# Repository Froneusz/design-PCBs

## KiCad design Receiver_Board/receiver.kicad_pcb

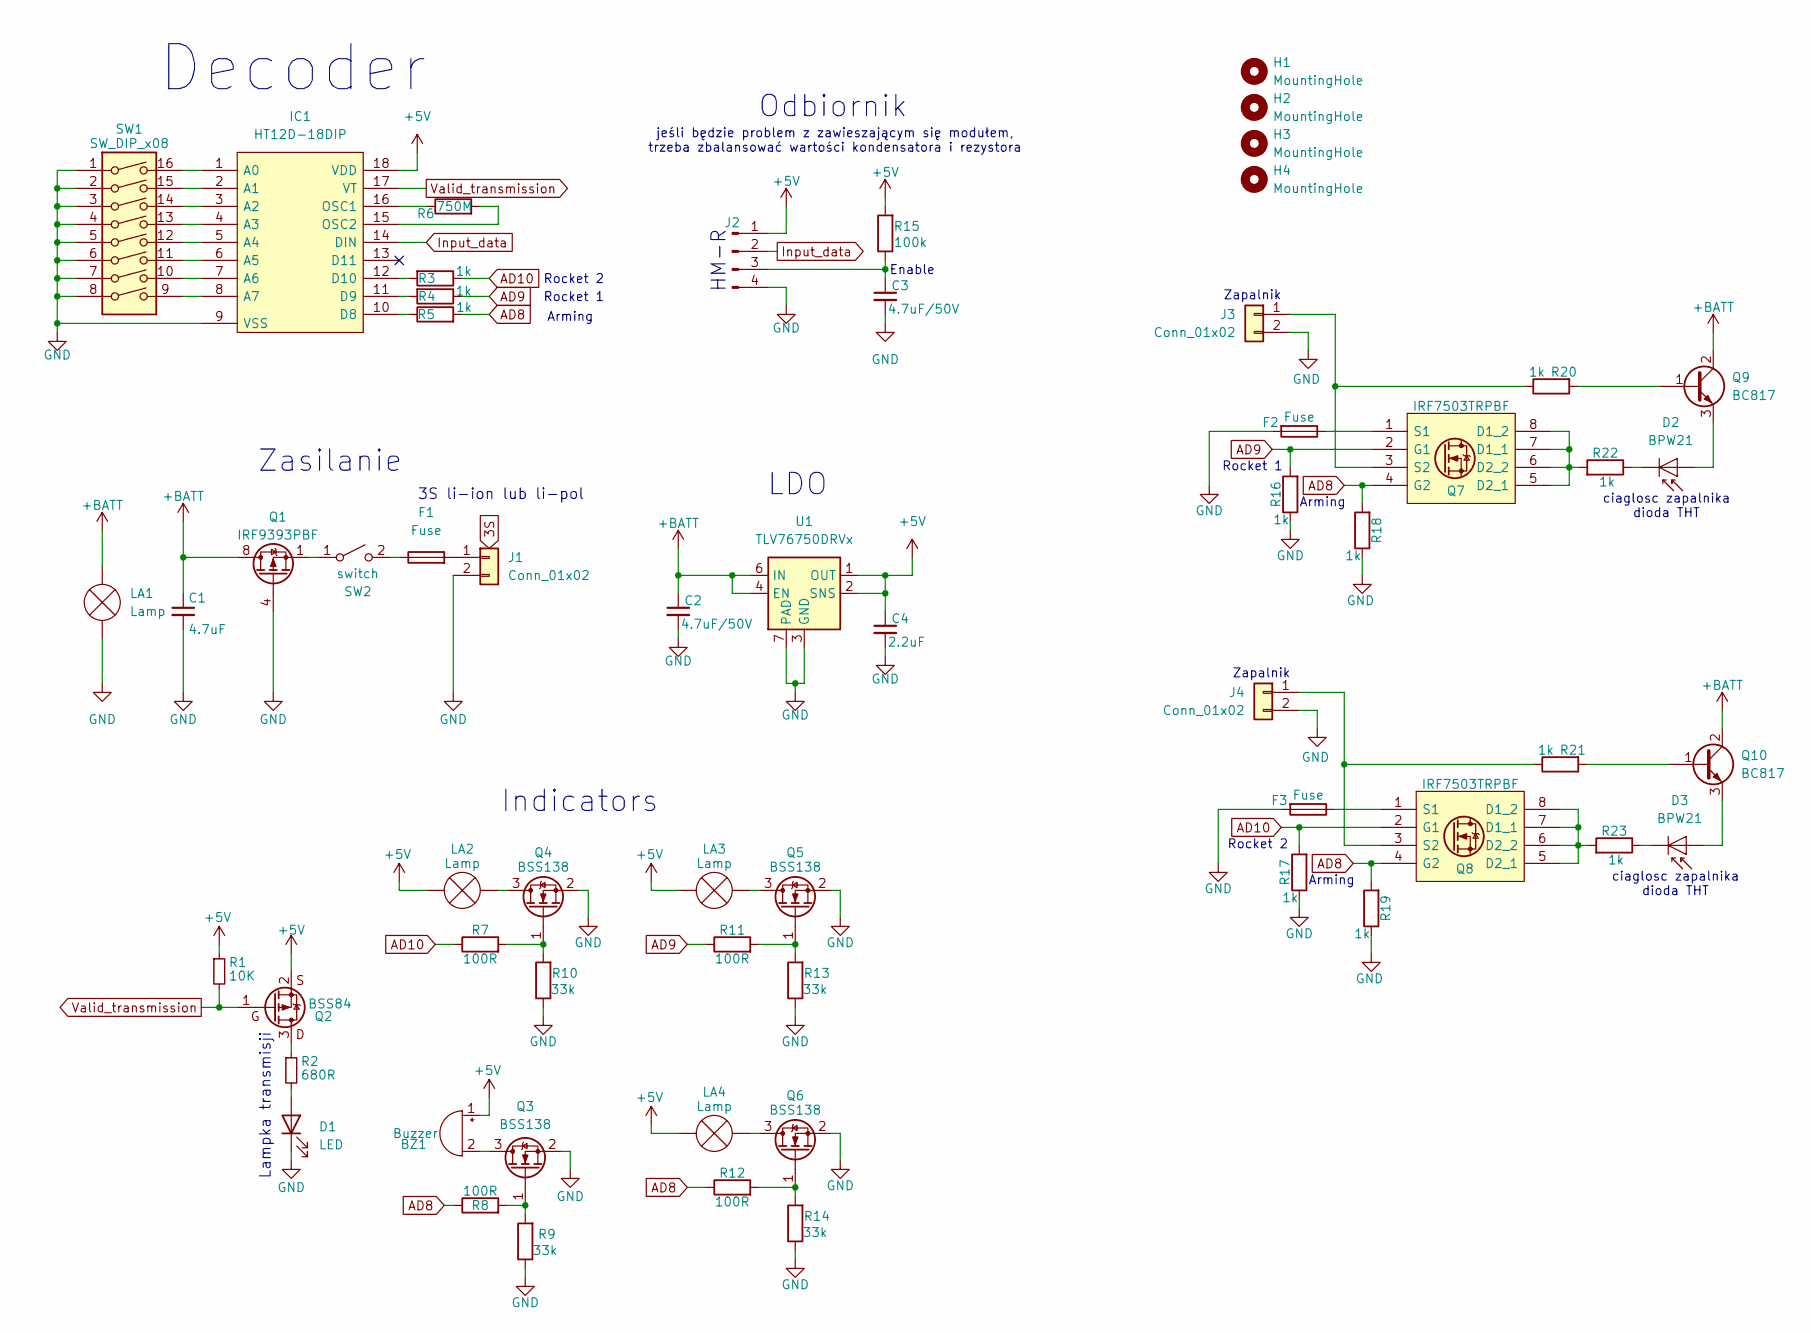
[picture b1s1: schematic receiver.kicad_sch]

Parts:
BZ1: Buzzer; PinHeader_1x02_P2.54mm_Vertical_led_relayboard_lpbox
C1: 4.7uF; C_0805_2012Metric_Pad1.18x1.45mm_HandSolder
C2, C3: 4.7uF/50V; C_0805_2012Metric_Pad1.18x1.45mm_HandSolder
C4: 2.2uF; C_0805_2012Metric_Pad1.18x1.45mm_HandSolder
D1: LED; LED_0603_1608Metric_Pad1.05x0.95mm_HandSolder
D2, D3: BPW21; PinHeader_1x02_P2.54mm_Vertical_led_relayboard_lpbox
F1, F2, F3: Fuse; Fuse_0805_2012Metric_Pad1.15x1.40mm_HandSolder
H1, H2, H3, H4: MountingHole; MountingHole_3.2mm_M3
IC1: HT12D-18DIP; DIP18 HT12; Manufacturer_Part_Number HT12D-18DIP
J1: Conn_01x02; XY2500R-DS(5.08)-02P
J2: Conn_01x04_Pin; PinHeader_1x04_P2.54mm_Vertical
J3, J4: Conn_01x02; PhoenixContact_MCV_1,5_2-G-3.5_1x02_P3.50mm_Vertical
LA1, LA2, LA3, LA4: Lamp; PinHeader_1x02_P2.54mm_Vertical_led_relayboard_lpbox
Q1: IRF9393PBF; SOIC-8_3.9x4.9mm_P1.27mm
Q2: BSS84; SOT-23
Q3, Q4, Q5, Q6: BSS138; SOT-23
Q7, Q8: IRF7503TRPBF; SOP65P490X110-8N; Mouser Part Number 942-IRF7503TRPBF
Q9, Q10: BC817; SOT-23_Handsoldering
R1: 10K; R_0603_1608Metric_Pad0.98x0.95mm_HandSolder
R2: 680R; R_0603_1608Metric_Pad0.98x0.95mm_HandSolder
R3, R4, R5, R16, R17, R18, R19, R20, R21, R22, R23: 1k; R_0603_1608Metric_Pad0.98x0.95mm_HandSolder
R6: 750M; R_0603_1608Metric_Pad0.98x0.95mm_HandSolder
R7, R8, R11, R12: 100R; R_0603_1608Metric_Pad0.98x0.95mm_HandSolder
R9, R10, R13, R14: 33k; R_0603_1608Metric_Pad0.98x0.95mm_HandSolder
R15: 100k; R_0603_1608Metric_Pad0.98x0.95mm_HandSolder
SW1: SW_DIP_x08; 2198MSTR
SW2: switch; PinHeader_1x02_P2.54mm_Vertical_led_relayboard_lpbox
U1: TLV76750DRVx; WSON-6-1EP_2x2mm_P0.65mm_EP1x1.6mm_ThermalVias

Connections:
+5V: BZ1.1 (+), C4.1, IC1.18 (VDD), J2.1, LA2.2 (+), LA3.2 (+), LA4.2 (+), Q2.2 (S), R1.1, R15.2, U1.1 (OUT), U1.2 (SNS)
+BATT: C1.1, C2.1, LA1.2 (+), Q1.5 (D), Q1.6 (D), Q1.7 (D), Q1.8 (D), Q9.2 (C), Q10.2 (C), U1.4 (EN), U1.6 (IN)
AD8: Q7.4 (G2), Q8.4 (G2), R5.2, R8.1, R12.1, R18.2, R19.2
AD9: Q7.2 (G1), R4.1, R11.1, R16.2
AD10: Q8.2 (G1), R3.1, R7.1, R17.2
GND: C1.2, C2.2, C3.2, C4.2, D1.1 (K), F2.2, F3.2, IC1.9 (VSS), J1.2, J2.4, J3.2, J4.2, LA1.1 (-), Q1.4 (G), Q3.2 (S), Q4.2 (S), Q5.2 (S), Q6.2 (S), R9.1, R10.1, R13.1, R14.1, R16.1, R17.1, R18.1, R19.1, SW1.1, SW1.2, SW1.3, SW1.4, SW1.5, SW1.6, SW1.7, SW1.8, U1.3 (GND), U1.5 (GND), U1.7 (PAD)
Input_data: IC1.14 (DIN), J2.2
unnamed: BZ1.2 (-), Q3.3 (D)
unnamed: D1.2 (A), R2.2
unnamed: D2.1 (A), Q9.3 (E)
unnamed: D2.2 (K), R22.1
unnamed: D3.1 (A), Q10.3 (E)
unnamed: D3.2 (K), R23.1
unnamed: IC1.1 (A0), SW1.16
unnamed: IC1.2 (A1), SW1.15
unnamed: IC1.3 (A2), SW1.14
unnamed: IC1.4 (A3), SW1.13
unnamed: IC1.5 (A4), SW1.12
unnamed: IC1.6 (A5), SW1.11
unnamed: IC1.7 (A6), SW1.10
unnamed: IC1.8 (A7), SW1.9
unnamed: IC1.10 (D8), R5.1
unnamed: IC1.11 (D9), R4.2
unnamed: IC1.12 (D10), R3.2
unnamed: IC1.16 (OSC1), R6.1
unnamed: IC1.15 (OSC2), R6.2
unnamed: F1.2, J1.1
unnamed: C3.1, J2.3, R15.1
unnamed: J3.1, Q7.3 (S2), R20.1
unnamed: J4.1, Q8.3 (S2), R21.1
unnamed: LA2.1 (-), Q4.3 (D)
unnamed: LA3.1 (-), Q5.3 (D)
unnamed: LA4.1 (-), Q6.3 (D)
unnamed: Q2.3 (D), R2.1
unnamed: Q3.1 (G), R8.2, R9.2
unnamed: Q4.1 (G), R7.2, R10.2
unnamed: Q5.1 (G), R11.2, R13.2
unnamed: Q6.1 (G), R12.2, R14.2
unnamed: Q7.5 (D2_1), Q7.6 (D2_2), Q7.7 (D1_1), Q7.8 (D1_2), R22.2
unnamed: F2.1, Q7.1 (S1)
unnamed: Q8.5 (D2_1), Q8.6 (D2_2), Q8.7 (D1_1), Q8.8 (D1_2), R23.2
unnamed: F3.1, Q8.1 (S1)
unnamed: Q9.1 (B), R20.2
unnamed: Q10.1 (B), R21.2
unnamed: Q1.1 (S), Q1.2 (S), Q1.3 (S), SW2.1 (A)
unnamed: F1.1, SW2.2 (B)
Valid_transmission: IC1.17 (VT), Q2.1 (G), R1.2

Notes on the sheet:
Rocket 1
LDO
jeśli będzie problem z zawieszającym się modułem, trzeba zbalansować wartości kondensatora i rezystora
Zasilanie
ciaglosc zapalnika dioda THT
Arming
Indicators
Rocket 2
Lampka transmisji
Odbiornik
Enable
HM-R
Zapalnik
Decoder
3S li-ion lub li-pol

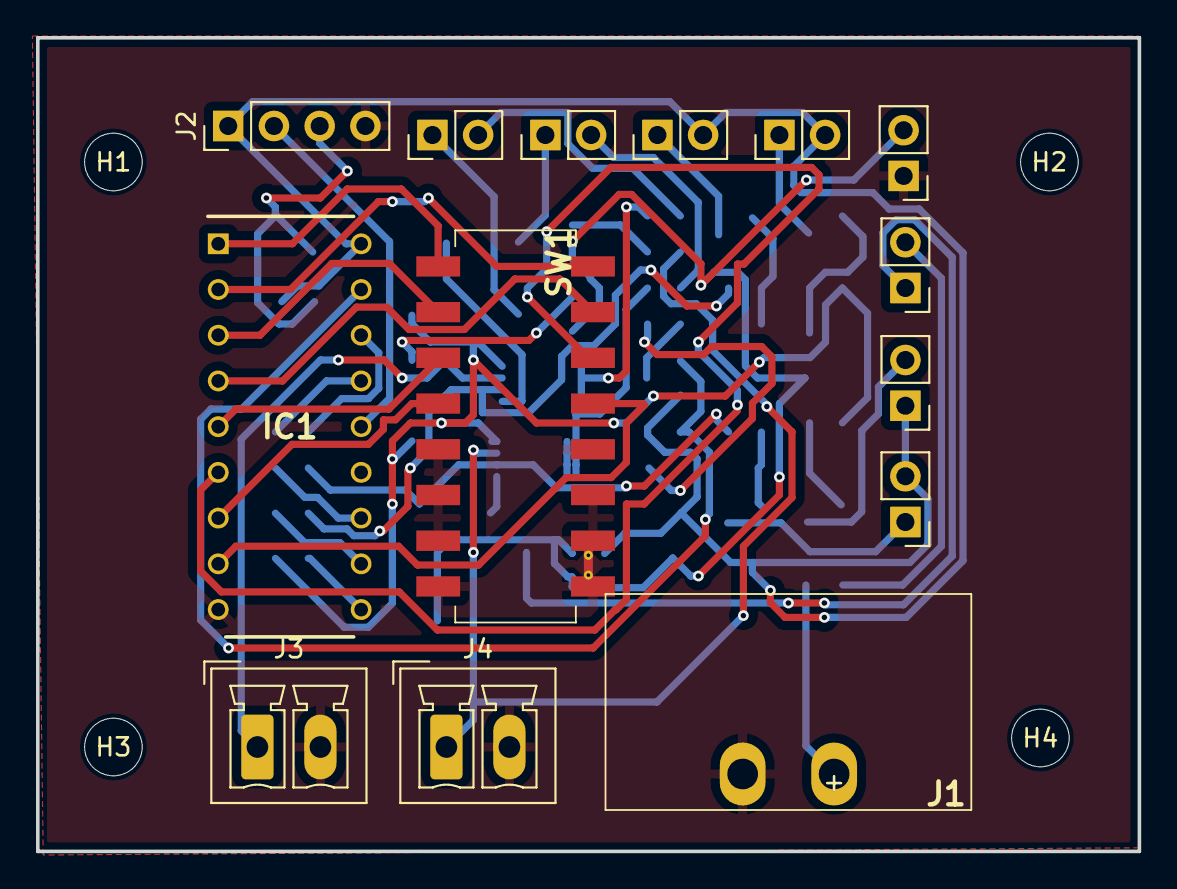
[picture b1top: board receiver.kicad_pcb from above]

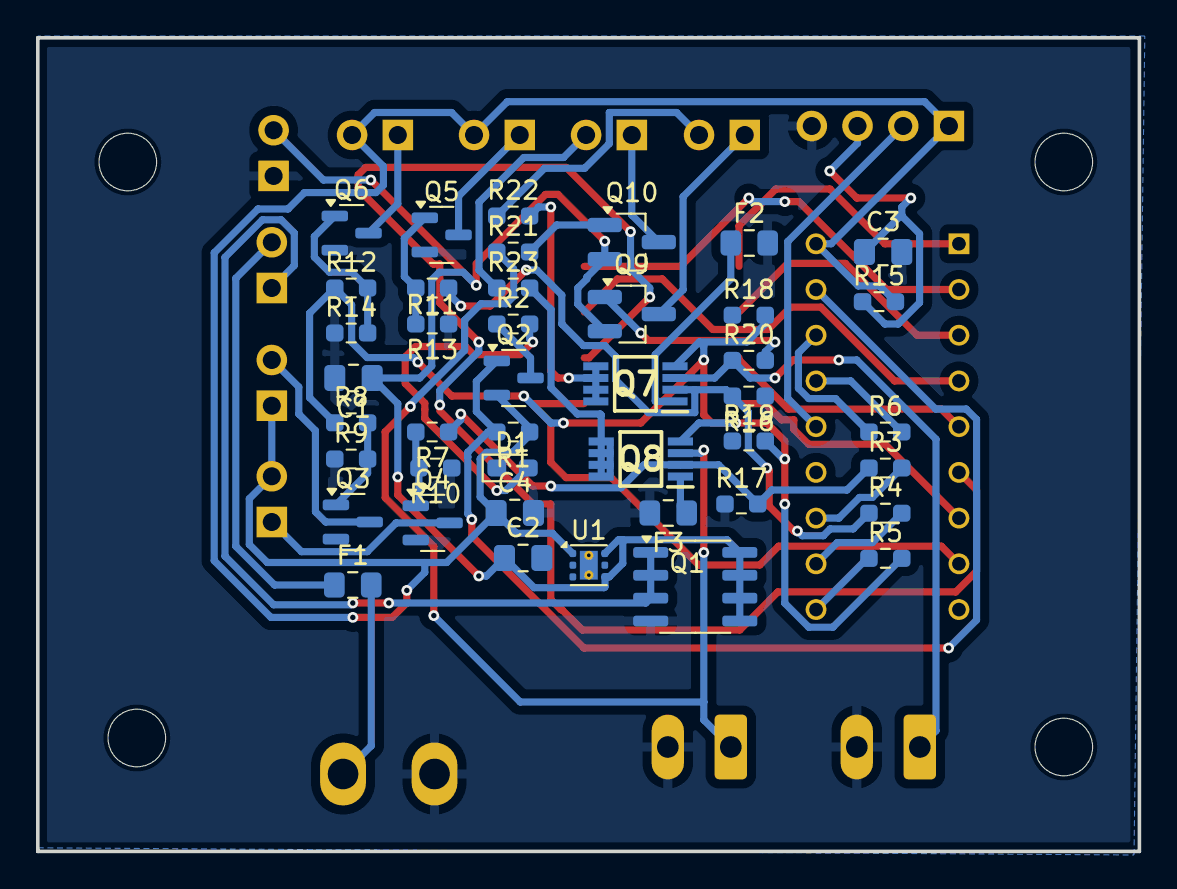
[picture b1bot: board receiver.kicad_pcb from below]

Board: 2 copper layers, 61.2 x 45.2 mm, 60 parts (42 on the bottom side), 47 nets.

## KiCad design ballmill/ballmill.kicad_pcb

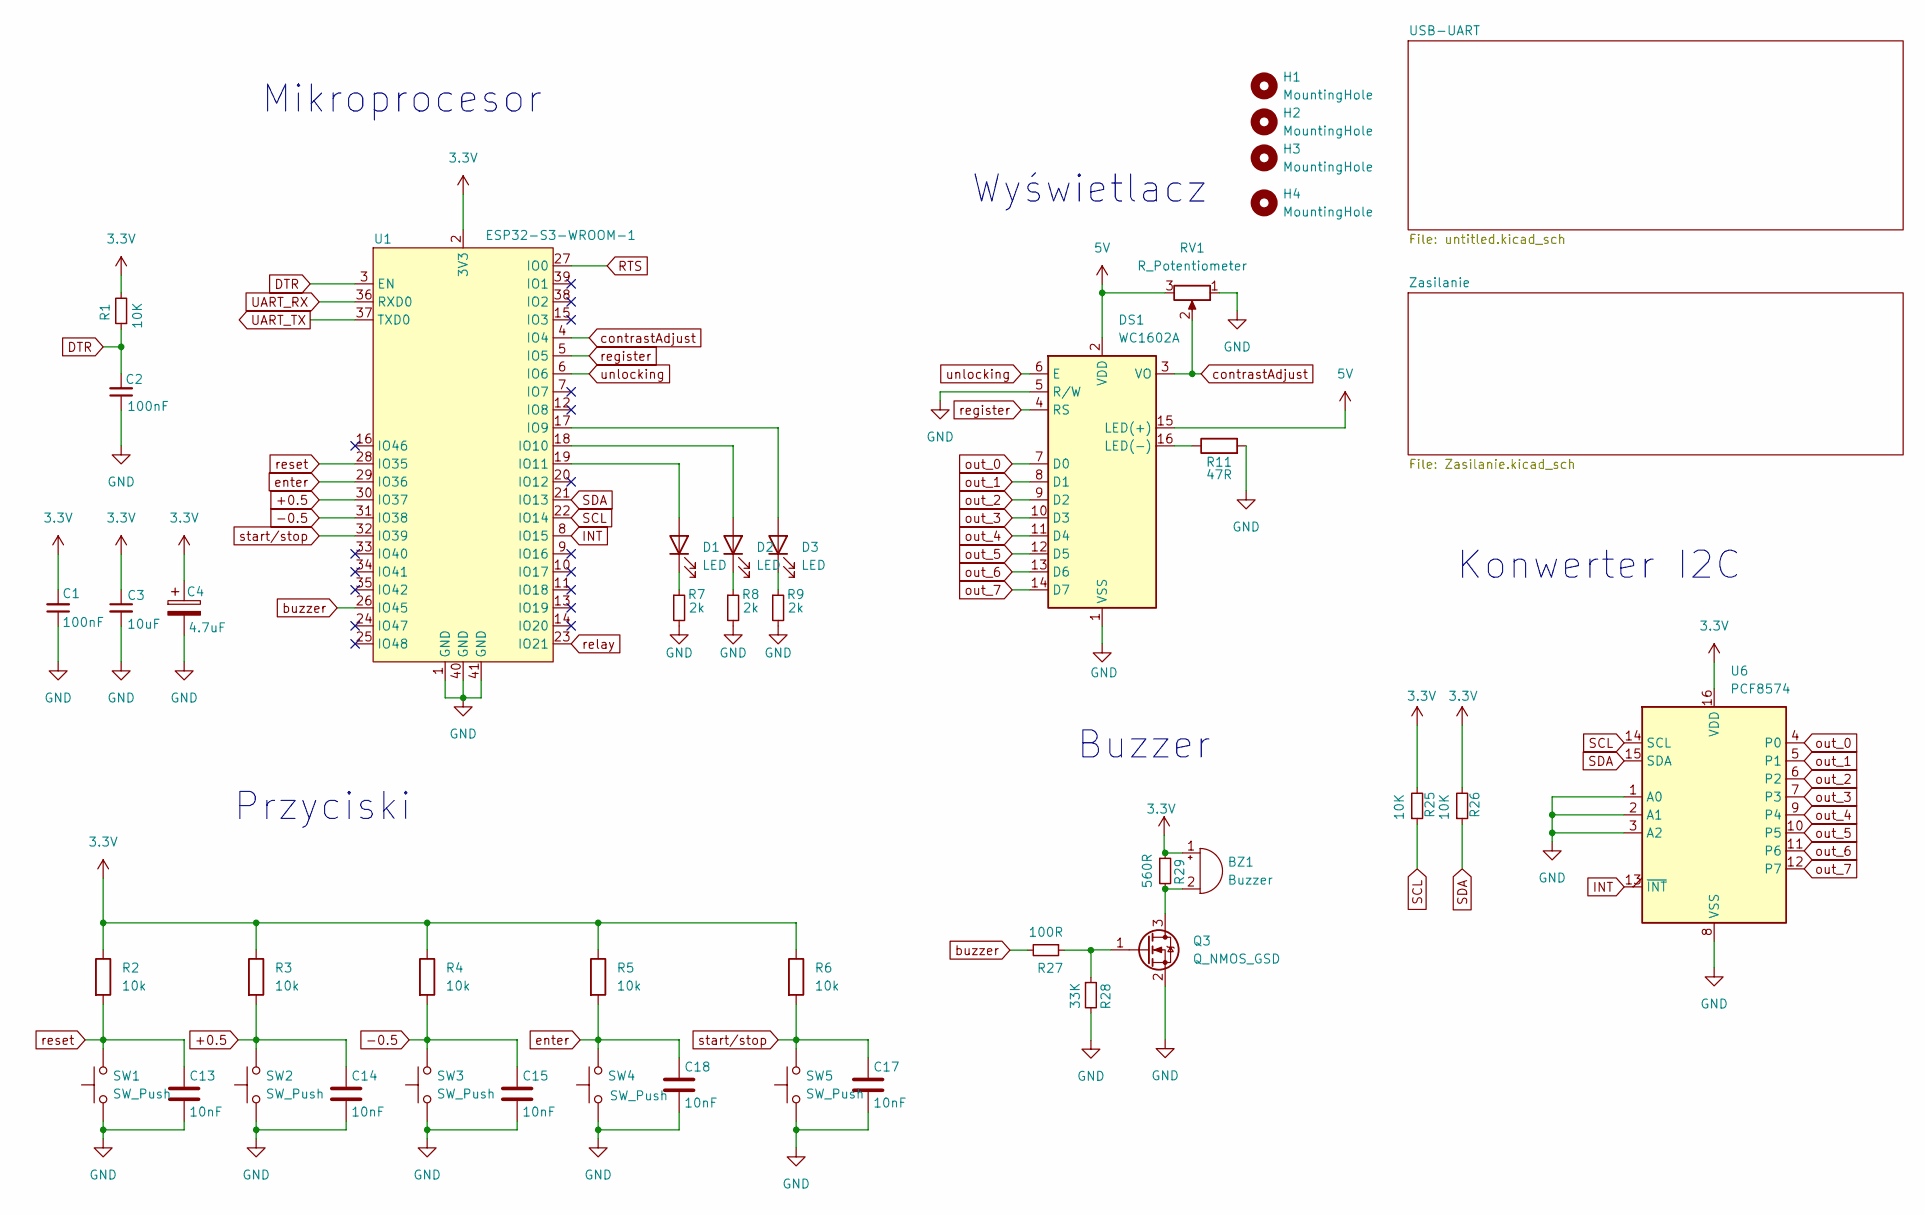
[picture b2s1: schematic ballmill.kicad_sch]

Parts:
BZ1: Buzzer; CMI9605IC0580T
C1, C2: 100nF; C_0603_1608Metric_Pad1.08x0.95mm_HandSolder
C3: 10uF; C_0603_1608Metric_Pad1.08x0.95mm_HandSolder
C4: 4.7uF; C_0603_1608Metric_Pad1.08x0.95mm_HandSolder
C13, C14, C15, C17, C18: 10nF; C_0603_1608Metric_Pad1.08x0.95mm_HandSolder
D1, D2, D3: LED; LED_0805_2012Metric_Pad1.15x1.40mm_HandSolder
DS1: WC1602A
H1, H2, H3, H4: MountingHole; MountingHole_3.2mm_M3
Q3: Q_NMOS_GSD; SOT-23_Handsoldering
R1, R25, R26: 10K; R_0603_1608Metric_Pad0.98x0.95mm_HandSolder
R2, R3, R4, R5, R6: 10k; R_0603_1608Metric_Pad0.98x0.95mm_HandSolder
R7, R8, R9: 2k; R_0603_1608Metric_Pad0.98x0.95mm_HandSolder
R11: 47R; R_0603_1608Metric_Pad0.98x0.95mm_HandSolder
R27: 100R; R_0603_1608Metric_Pad0.98x0.95mm_HandSolder
R28: 33K; R_0603_1608Metric_Pad0.98x0.95mm_HandSolder
R29: 560R; R_0603_1608Metric_Pad0.98x0.95mm_HandSolder
RV1: R_Potentiometer; Potentiometer_Bourns_3296W_Vertical
SW1, SW2, SW3, SW4, SW5: SW_Push; SW_PUSH_6mm
U1: ESP32-S3-WROOM-1
U6: PCF8574; QFN50P300X300X100-17N-D

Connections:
3.3V: BZ1.1 (-), C1.2, C3.1, C4.1, R1.2, R2.1, R3.1, R4.1, R5.1, R6.1, R25.2, R26.2, R29.1, U1.2 (3V3), U6.16 (VDD); also elsewhere on the board
5V: DS1.2 (VDD), DS1.15 (LED(+)), RV1.3; also elsewhere on the board
+0.5: C14.2, R3.2, SW2.2, U1.30 (IO37)
-0.5: C15.2, R4.2, SW3.2, U1.31 (IO38)
DTR: C2.2, R1.1, U1.3 (EN); also elsewhere on the board
GND: C1.1, C2.1, C3.2, C4.2, C13.1, C14.1, C15.1, C17.1, C18.1, DS1.1 (VSS), DS1.5 (R/W), Q3.2 (S), R7.2, R8.2, R9.2, R11.2, R28.2, RV1.1, SW1.1, SW2.1, SW3.1, SW4.1, SW5.1, U1.1 (GND), U1.40 (GND), U1.41 (GND), U6.1 (A0), U6.2 (A1), U6.3 (A2), U6.8 (VSS); also elsewhere on the board
INT: U1.8 (IO15), U6.13 (~INT)
unnamed: BZ1.2 (+), Q3.3 (D), R29.2
unnamed: D1.2 (A), U1.19 (IO11)
unnamed: D1.1 (K), R7.1
unnamed: D2.2 (A), U1.18 (IO10)
unnamed: D2.1 (K), R8.1
unnamed: D3.2 (A), U1.17 (IO9)
unnamed: D3.1 (K), R9.1
unnamed: DS1.16 (LED(-)), R11.1
unnamed: Q3.1 (G), R27.1, R28.1
RTS: U1.27 (IO0); also elsewhere on the board
SCL: R25.1, U1.22 (IO14), U6.14 (SCL)
SDA: R26.1, U1.21 (IO13), U6.15 (SDA)
UART_RX: U1.36 (RXD0); also elsewhere on the board
UART_TX: U1.37 (TXD0); also elsewhere on the board
buzzer: R27.2, U1.26 (IO45)
contrastAdjust: DS1.3 (VO), RV1.2, U1.4 (IO4)
enter: C18.2, R5.2, SW4.2, U1.29 (IO36)
out_0: DS1.7 (D0), U6.4 (P0)
out_1: DS1.8 (D1), U6.5 (P1)
out_2: DS1.9 (D2), U6.6 (P2)
out_3: DS1.10 (D3), U6.7 (P3)
out_4: DS1.11 (D4), U6.9 (P4)
out_5: DS1.12 (D5), U6.10 (P5)
out_6: DS1.13 (D6), U6.11 (P6)
out_7: DS1.14 (D7), U6.12 (P7)
register: DS1.4 (RS), U1.5 (IO5)
relay: U1.23 (IO21); also elsewhere on the board
reset: C13.2, R2.2, SW1.2, U1.28 (IO35)
start/stop: C17.2, R6.2, SW5.2, U1.32 (IO39)
unlocking: DS1.6 (E), U1.6 (IO6)

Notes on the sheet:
Mikroprocesor
Konwerter I2C
Buzzer
Wyświetlacz
Przyciski

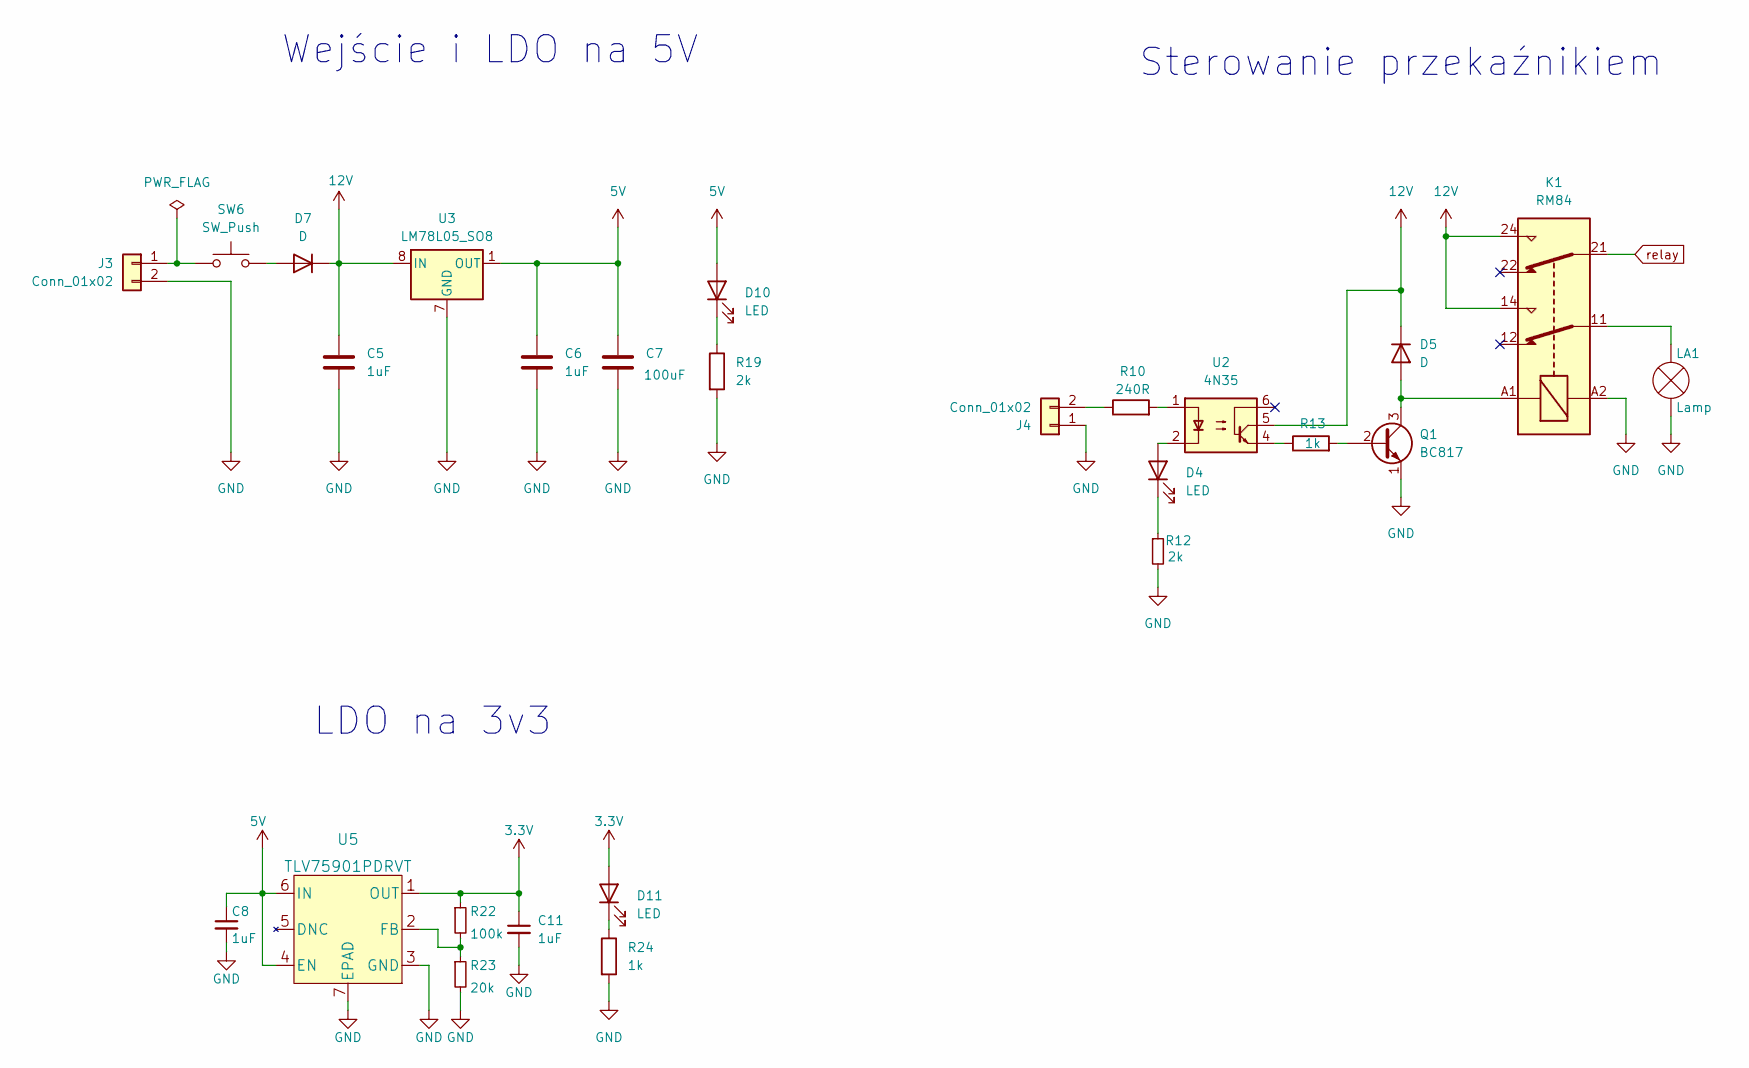
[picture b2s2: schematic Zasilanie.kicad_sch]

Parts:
C5, C6, C8, C11: 1uF; C_0805_2012Metric_Pad1.18x1.45mm_HandSolder
C7: 100uF; C_0805_2012Metric_Pad1.18x1.45mm_HandSolder
D4, D10, D11: LED; LED_0805_2012Metric_Pad1.15x1.40mm_HandSolder
D5: D; PinHeader_1x02_P2.54mm_Vertical_led_relayboard_lpbox
D7: D; D_0805_2012Metric_Pad1.15x1.40mm_HandSolder
J3, J4: Conn_01x02; XY2500R-DS(5.08)-02P
K1: RM84; Relay_DPDT_Finder_40.52
LA1: Lamp; PinHeader_1x02_P2.54mm_Vertical_led_relayboard_lpbox
Q1: BC817; SOT-23_Handsoldering
R10: 240R; R_0603_1608Metric_Pad0.98x0.95mm_HandSolder
R12, R19: 2k; R_0603_1608Metric_Pad0.98x0.95mm_HandSolder
R13, R24: 1k; R_0603_1608Metric_Pad0.98x0.95mm_HandSolder
R22: 100k; R_0805_2012Metric_Pad1.20x1.40mm_HandSolder
R23: 20k; R_0805_2012Metric_Pad1.20x1.40mm_HandSolder
SW6: SW_Push; SW_PUSH_6mm
U2: 4N35; DIP-6_W7.62mm
U3: LM78L05_SO8; SOIC-8_3.9x4.9mm_P1.27mm
U5: TLV75901PDRVT

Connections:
3.3V: C11.1, D11.2 (A), R22.1, U5.1 (OUT); also elsewhere on the board
5V: C6.1, C7.1, C8.1, D10.2 (A), U3.1 (OUT), U5.4 (EN), U5.6 (IN); also elsewhere on the board
12V: C5.1, D5.1 (K), D7.1 (K), K1.14, K1.24, U2.5, U3.8 (IN)
GND: C5.2, C6.2, C7.2, C8.2, C11.2, J3.2, J4.1, K1.A2, LA1.1 (-), Q1.1 (E), R12.2, R19.2, R23.2, R24.2, U3.2 (GND), U3.3 (GND), U3.6 (GND), U3.7 (GND), U5.3 (GND), U5.7 (EPAD); also elsewhere on the board
unnamed: D4.2 (A), U2.2
unnamed: D4.1 (K), R12.1
unnamed: D5.2 (A), K1.A1, Q1.3 (C)
unnamed: D7.2 (A), SW6.2
unnamed: D10.1 (K), R19.1
unnamed: D11.1 (K), R24.1
unnamed: J3.1, SW6.1
unnamed: J4.2, R10.1
unnamed: K1.11, LA1.2 (+)
unnamed: Q1.2 (B), R13.2
unnamed: R10.2, U2.1
unnamed: R13.1, U2.4
unnamed: R22.2, R23.1, U5.2 (FB)
relay: K1.21; also elsewhere on the board

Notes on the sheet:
Sterowanie przekaźnikiem
LDO na 3v3
Wejście i LDO na 5V

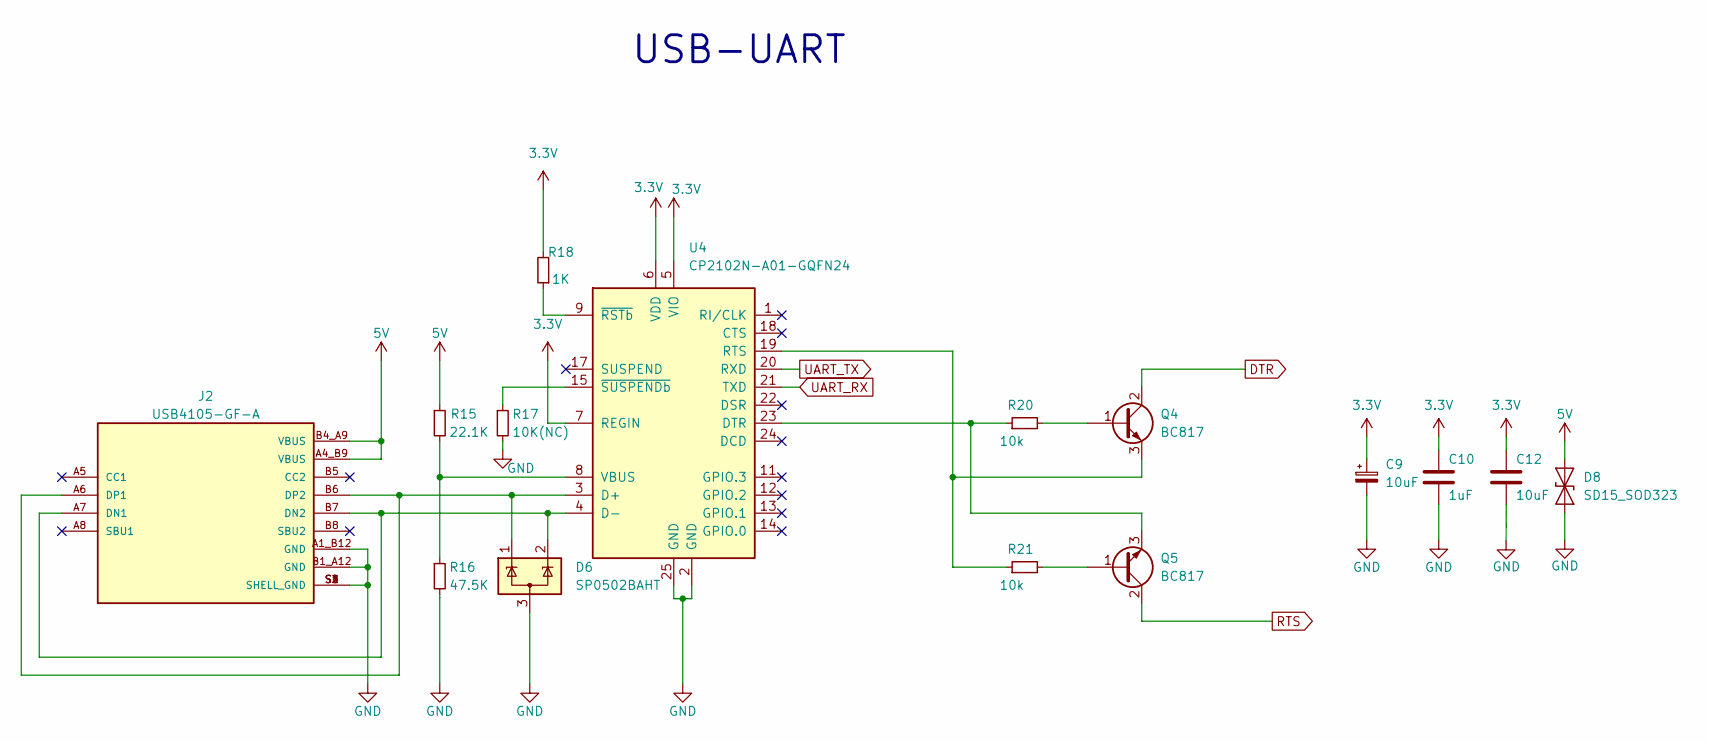
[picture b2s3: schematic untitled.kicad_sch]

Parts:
C9: 10uF; C_1206_3216Metric_Pad1.33x1.80mm_HandSolder
C10: 1uF; C_0603_1608Metric_Pad1.08x0.95mm_HandSolder
C12: 10uF; C_0805_2012Metric_Pad1.18x1.45mm_HandSolder
D6: SP0502BAHT; SOT-23
D8: SD15_SOD323; D_0805_2012Metric
J2: USB4105-GF-A; GCT_USB4105-GF-A; PARTREV A3
Q4, Q5: BC817; SOT-23_Handsoldering
R15: 22.1K; R_0603_1608Metric_Pad0.98x0.95mm_HandSolder
R16: 47.5K; R_0603_1608Metric_Pad0.98x0.95mm_HandSolder
R17: 10K(NC); R_0603_1608Metric_Pad0.98x0.95mm_HandSolder
R18: 1K; R_0603_1608Metric_Pad0.98x0.95mm_HandSolder
R20, R21: 10k; R_0603_1608Metric_Pad0.98x0.95mm_HandSolder
U4: CP2102N-A01-GQFN24; QFN-24-1EP_4x4mm_P0.5mm_EP2.6x2.6mm

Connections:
3.3V: C9.1, C10.2, C12.1, R18.2, U4.5 (VIO), U4.6 (VDD), U4.7 (REGIN); also elsewhere on the board
5V: D8.2 (A2), J2.A4_B9 (VBUS), J2.B4_A9 (VBUS), R15.1; also elsewhere on the board
DTR: Q4.2 (C); also elsewhere on the board
GND: C9.2, C10.1, C12.2, D6.3 (A), D8.1 (A1), J2.A1_B12 (GND), J2.B1_A12 (GND), J2.S1 (SHELL_GND), J2.S2 (SHELL_GND), J2.S3 (SHELL_GND), J2.S4 (SHELL_GND), R16.2, R17.2, U4.2 (GND), U4.25 (GND); also elsewhere on the board
unnamed: D6.2 (K), J2.A7 (DN1), J2.B7 (DN2), U4.4 (D-)
unnamed: D6.1 (K), J2.A6 (DP1), J2.B6 (DP2), U4.3 (D+)
unnamed: Q4.1 (B), R20.2
unnamed: Q4.3 (E), R21.1, U4.19 (RTS)
unnamed: Q5.1 (B), R21.2
unnamed: Q5.3 (E), R20.1, U4.23 (DTR)
unnamed: R15.2, R16.1, U4.8 (VBUS)
unnamed: R18.1, U4.9 (~RSTb)
unnamed: R17.1, U4.15 (~SUSPENDb)
RTS: Q5.2 (C); also elsewhere on the board
UART_RX: U4.21 (TXD); also elsewhere on the board
UART_TX: U4.20 (RXD); also elsewhere on the board

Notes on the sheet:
USB-UART

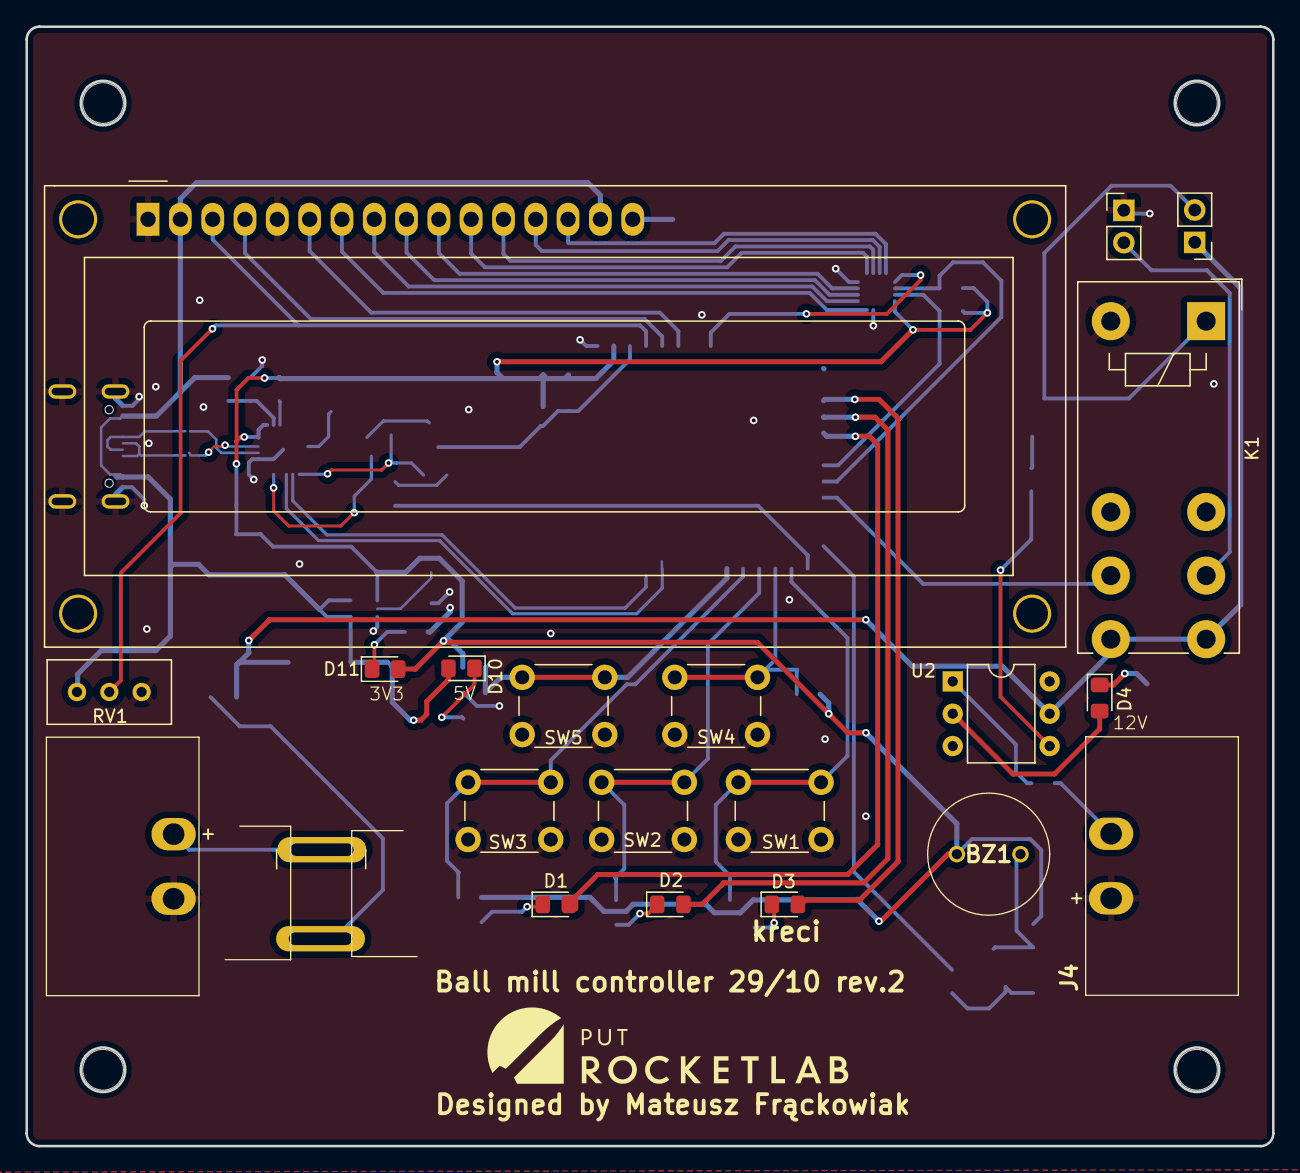
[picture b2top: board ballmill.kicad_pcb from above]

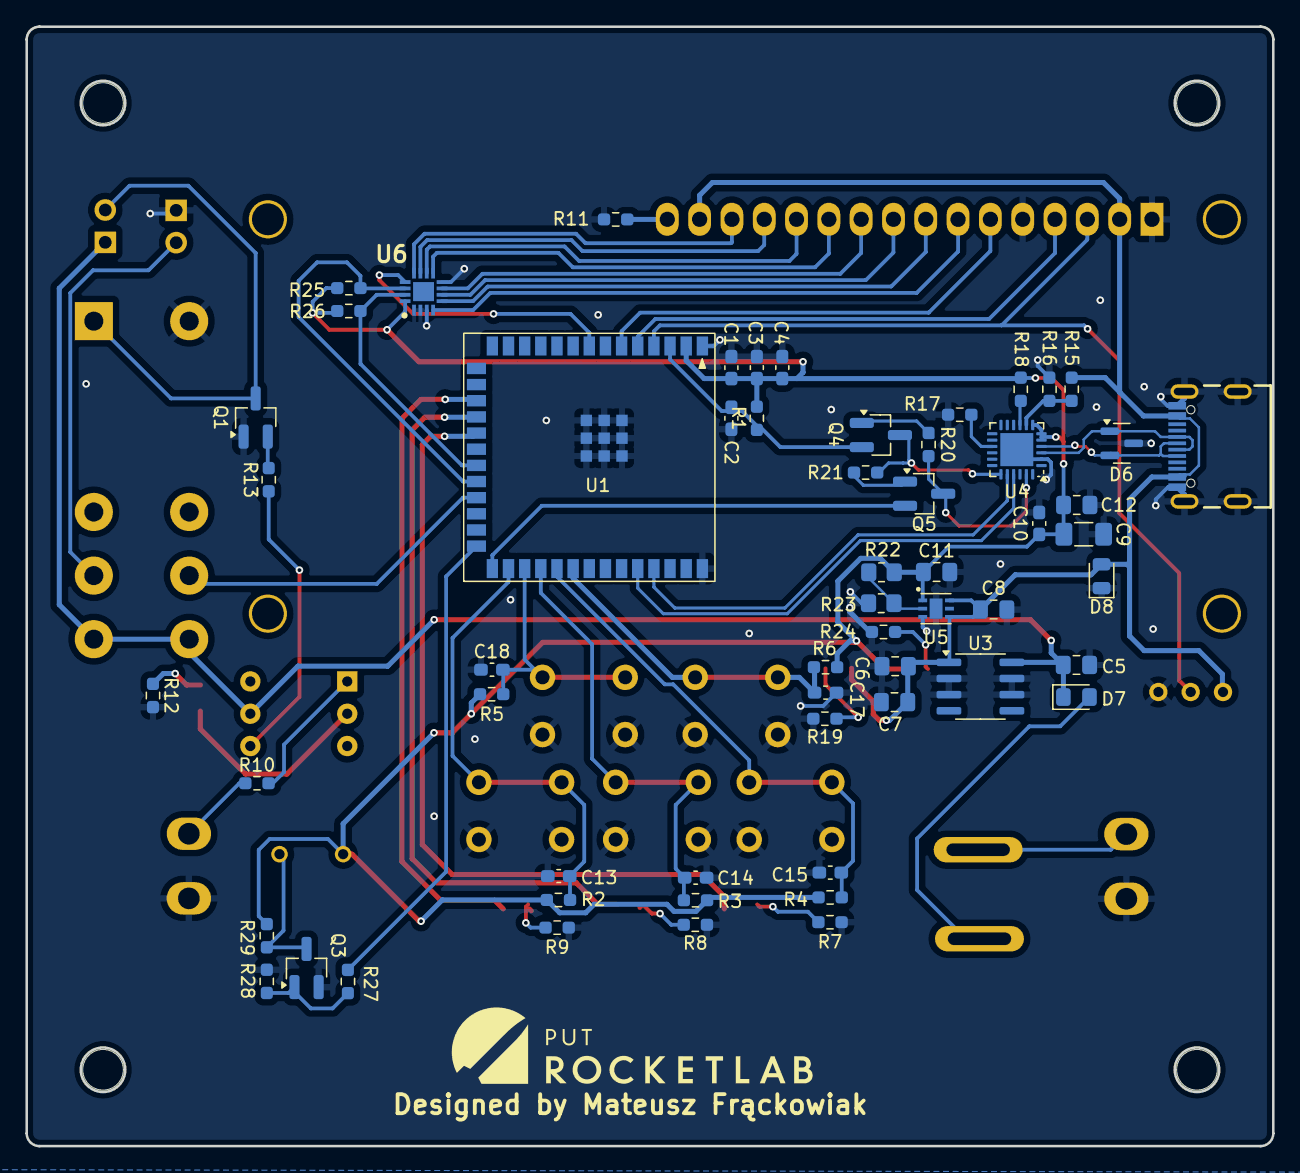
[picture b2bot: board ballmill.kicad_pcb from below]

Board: 2 copper layers, 98.0 x 88.0 mm, 83 parts (58 on the bottom side), 60 nets.

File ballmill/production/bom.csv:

Designator,Footprint,Quantity,Value,LCSC Part #
Buzzer1,Buzzer_fi10mm_P5mm,1,CMI-9605IC-0580T,
"C1, C3",0603,2,100nF,
"C10, C2",0603,2,1uF,
"C11, C5, C6, C8",0805,4,1uF,
"C12, C4",0805,2,10uF,
C7,0805,1,100uF,
C9,1206,1,10uF,
"D1, D10, D11, D2, D3, D4, D7",0805,7,LED,
D5,PinHeader_1x02_P2.54mm_Vertical_led_relayboard_lpbox,1,D,
D6,SOT-23,1,SP0502BAHT,
D8,0805,1,SD15_SOD323,
DS1,WC1602A,1,WC1602A,
F1,0805,1,Fuse,
"J1, J3",XY2500R-DS(5.08)-02P,2,Conn_01x02,
J2,GCT_USB4105-GF-A,1,USB4105-GF-A,
K1,Relay_DPDT_Finder_40.52,1,RM84,
LA1,PinHeader_1x02_P2.54mm_Vertical_led_relayboard_lpbox,1,Lamp,
Q2,SOT-23,1,BSS138,
Q3,SOIC-8_3.9x4.9mm_P1.27mm,1,IRF9393PBF,
"Q4, Q5, Q6",SOT-23_Handsoldering,3,BC817,
"R1, R2, R20, R21, R3, R4, R5, R6",0603,8,10k,
R10,0603,1,240R,
R11,0603,1,47R,
"R12, R18, R19, R25, R26",0603,5,1k,
R13,0603,1,100R,
R14,0603,1,33k,
R15,0603,1,22.1K,
R16,0603,1,47.5K,
R17,0603,1,10K(NC),
R22,0805,1,100k,
R23,0805,1,20k,
"R7, R8, R9",0603,3,2k,
RV1,Potentiometer_Bourns_3296W_Vertical,1,R_Potentiometer,
"SW1, SW2, SW3, SW4, SW5, SW6",SW_PUSH_6mm,6,SW_Push,
U1,ESP32-S3-WROOM-1,1,ESP32-S3-WROOM-1,
U2,DIP-6_W7.62mm,1,4N35,
U3,SOIC-8_3.9x4.9mm_P1.27mm,1,LM78L05_SO8,
U4,QFN-24-1EP_4x4mm_P0.5mm_EP2.6x2.6mm,1,CP2102N-A01-GQFN24,
U5,TLV75901PDRVT,1,TLV75901PDRVT,

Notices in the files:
parts and their libraries:
Copyright 2021 Accelerated Designs. All rights reserved.
